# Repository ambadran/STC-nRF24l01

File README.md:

# STC MCU nRF24l01 Interfacing

Allows any mc251-based STC MCU to easily read and write to/from nRF24l01. As well as providing all the other more advanced functions.

This library is built on `uni-stc` for Low-level hardware inits (SPI).

The nrf24l01 interfacing is mainly based on `ebrezadev` C implementation on Github, found in:
https://github.com/ebrezadev/nRF24L01-C-Driver

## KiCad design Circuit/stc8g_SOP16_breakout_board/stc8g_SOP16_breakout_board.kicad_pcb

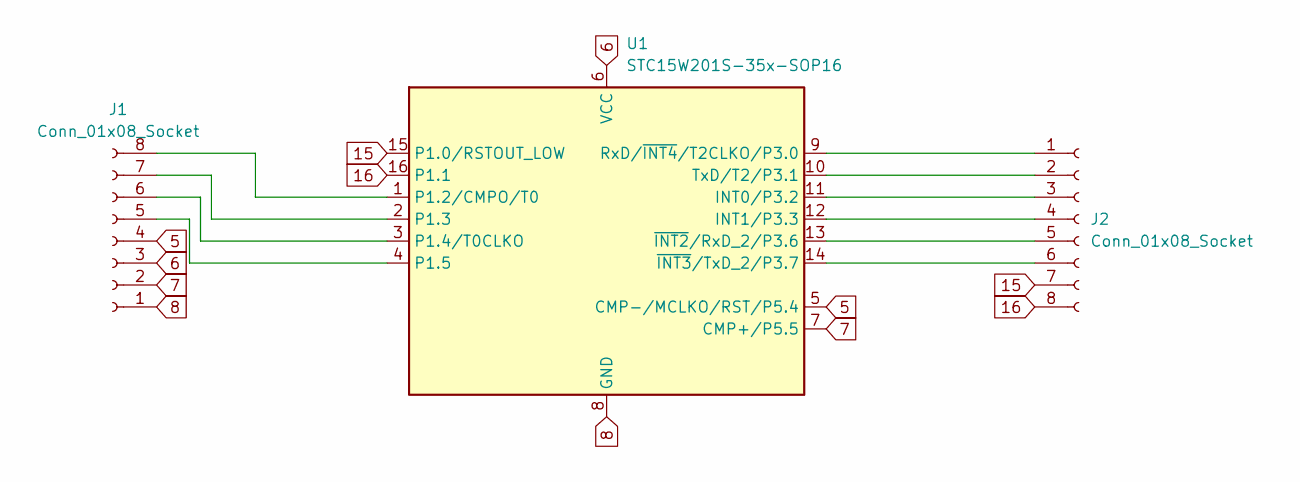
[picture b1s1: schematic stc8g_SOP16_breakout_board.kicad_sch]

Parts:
J1, J2: Conn_01x08_Socket; PinSocket_1x08_P2.54mm_Vertical
U1: STC15W201S-35x-SOP16; STC_SOP-16_3.9x9.9mm_P1.27mm

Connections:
5: J1.4, U1.5 (CMP-/MCLKO/RST/P5.4)
6: J1.3, U1.6 (VCC)
7: J1.2, U1.7 (CMP+/P5.5)
8: J1.1, U1.8 (GND)
15: J2.7, U1.15 (P1.0/RSTOUT_LOW)
16: J2.8, U1.16 (P1.1)
unnamed: J1.5, U1.4 (P1.5)
unnamed: J1.6, U1.3 (P1.4/T0CLKO)
unnamed: J1.7, U1.2 (P1.3)
unnamed: J1.8, U1.1 (P1.2/CMPO/T0)
unnamed: J2.1, U1.9 (RxD/~INT4/T2CLKO/P3.0)
unnamed: J2.2, U1.10 (TxD/T2/P3.1)
unnamed: J2.3, U1.11 (INT0/P3.2)
unnamed: J2.4, U1.12 (INT1/P3.3)
unnamed: J2.5, U1.13 (~INT2/RxD_2/P3.6)
unnamed: J2.6, U1.14 (~INT3/TxD_2/P3.7)

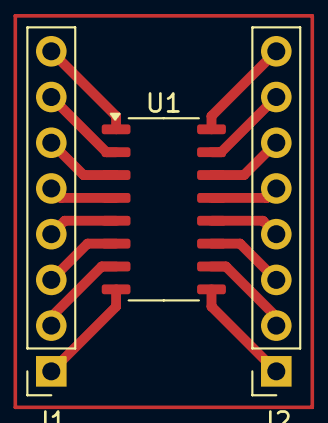
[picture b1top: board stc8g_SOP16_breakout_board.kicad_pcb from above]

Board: 2 copper layers, 3 parts (0 on the bottom side), 16 nets.

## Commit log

2024-03-28 finished stc8g1k08 breakout board and makefiles
2024-03-30 further development in file structure
2024-03-30 further development in nrf24 lib
2024-03-31 further development in nrf24
2024-04-01 further dev
2024-04-02 added bit reversal functionality
2024-04-04 finally can successfully read and write to nrf24 through stc ;)
2024-04-06 fur dev
2024-04-06 finally data is being sent from micropython to stc ;)
2024-04-08 wrote convenience methods for nrf, tested it with leds ;)
2024-06-15 file re-organise
2025-01-29 modified gitignore
2025-01-29 started development for sending through nrf
2025-01-31 started V2
2025-02-01 two STC MCUs now send and receive from each other properly ;)
2025-02-02 finally established ultimate dominion over the nRF24 module
2025-04-21 fixed some reliability bugs
2025-04-21 added photos of working registers
2025-06-09 fixed bug where padding didn't work because i>0 in loop
